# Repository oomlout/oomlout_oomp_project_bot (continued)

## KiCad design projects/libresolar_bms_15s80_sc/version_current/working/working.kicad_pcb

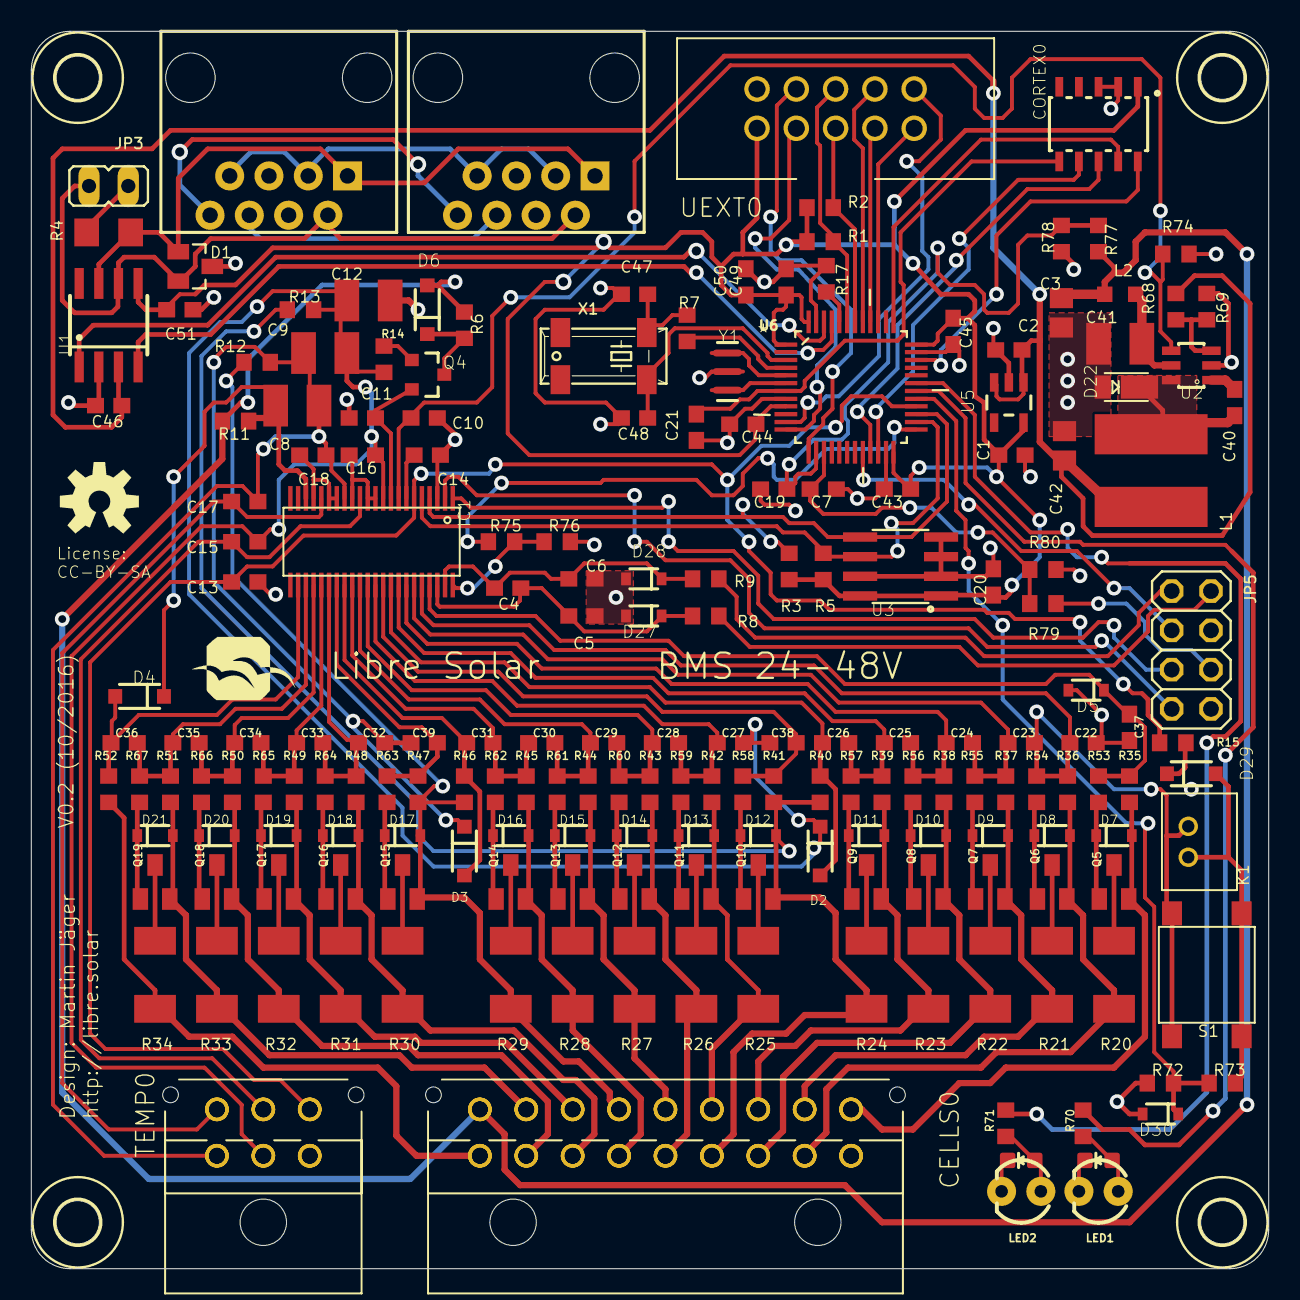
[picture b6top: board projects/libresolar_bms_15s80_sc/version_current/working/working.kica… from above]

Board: 2 copper layers, 80.0 x 80.0 mm, 201 parts (0 on the bottom side), 133 nets.

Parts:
C1, C50: 2.2µ; C0603
C2, C10, C11, C14, C16, C18: 1µ; C0603
C3: 1µ; C0805
C4, C5, C6, C7, C19, C20, C21, C22, C23, C24, C25, C26, C27, C28, C29, C30, C31, C32, C33, C34, C35, C36, C37, C38, C39, C40, C43, C44, C45, C46, C49, C51: 100n; C0603
C8, C9, C12: 10µ; C1210
C13, C15, C17: 4.7n; C0603
C41: 2.2µ; C1210
C42: 22µ; C0805
C47, C48: 4.3p; C0603
CELLS0: 66201821022
CORTEX0: CORTEX_DEBUGSMD; SAMTECH_FTSH-105-01
D1: NUP2105L; SOT23
D2, D3, D4, D6, D29: 1N4148W; SOD-123
D5, D27, D28, D30: 3.3V; SOD-323
D7, D8, D9, D10, D11, D12, D13, D14, D15, D16, D17, D18, D19, D20, D21: 5.6V; SOD-323
D22: DFLS1100-7; POWERDI123
D24, D26: LED-0603
H1, H2, H3, H4: MOUNT-HOLE2.8; 2,8
IC1: BQ76940; TSSOP44
JP1, JP2: RJ45; RJ45-8
JP3: JP1
JP5: 2X04
K1: 62000211622
K4: 66200621122
K5: 66201821122
L1: 47uH; WE-TPC_6823
L2: 4.7uH; L2012C
LED1, LED2: LED3MM
N1: OSHW-LOGOM; OSHW-LOGO-M
Q4: BSS123; SOT23-3
Q5, Q6, Q7, Q8, Q9, Q10, Q11, Q12, Q13, Q14, Q15, Q16, Q17, Q18, Q19: DMN2004K; SOT23
R1, R2, R3, R5: 2.2k; R0603
R4: 120; R1206
R6: t.b.d.; R0603
R7: 0R; R0603
R8, R9, R35, R36, R37, R38, R39, R40, R41, R42, R43, R44, R45, R46, R47, R48, R49, R50, R51, R52, R75: 1k; R0603
R11, R12, R13: 100; R0603
R14, R72, R74, R77, R79: 100k; R0603
R15, R78, R80: 5.6k; R0603
R17, R53, R54, R55, R56, R57, R58, R59, R60, R61, R62, R63, R64, R65, R66, R67, R69, R73: 10k; R0603
R20, R21, R22, R23, R24, R25, R26, R27, R28, R29, R30, R31, R32, R33, R34: 33; R2010
R68: 56k; R0603
R70, R71: 330; R0603
R76: 1M; R0603
S1: 430182050816
TEMP0: 66200621022
U1: TJA1042T/3; SOIC-8-N
U2: LMR16006X; SOT23-6
U3: M24256-BW; SO08
U5: MIC5225; SOT23-5
U6: STM32F072CB; QFP50P900X900X160-48N
U$1: LIBRESOLAR_LOGO
UEXT0: UEXT
X1: ABS25-32.768KHZ-6; MM20SS
Y1: 8MHz; RESONATOR-SMD-1_1

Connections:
+3V3: C1.1, C20.1, C43.1, C44.1, C45.1, C49.1, C50.1, C51.1, CORTEX0.1, R1.2, R2.2, R3.2, R5.2, U1.5, U3.1, U3.8, U5.5, U6.1, U6.9, U6.24, U6.36, U6.48, UEXT0.1
+5V: C2.1, C42.1, C46.1, L1.2, R68.2, U1.3, U5.1, U5.3
ALERT: IC1.44, R75.1, R76.2
ALERT_IN: R75.2, U6.25
BAT: C8.1, D4.C, IC1.20, R11.2
BTN: D30.C, R72.2, R73.1, U6.29
C0: CELLS0.10, D7.A, K5.10, Q5.2, R35.1
C1: CELLS0.2, D8.A, K5.2, Q6.2, R20.1, R36.1
C2: CELLS0.11, D9.A, K5.11, Q7.2, R21.1, R37.1
C3: CELLS0.3, D10.A, K5.3, Q8.2, R22.1, R38.1
C4: CELLS0.12, D11.A, K5.12, Q9.2, R23.1, R39.1
C5: CELLS0.4, D12.A, K5.4, Q10.2, R13.1, R24.1, R40.1, R41.1
C6: CELLS0.13, D13.A, K5.13, Q11.2, R25.1, R42.1
C7: CELLS0.5, D14.A, K5.5, Q12.2, R26.1, R43.1
C8: CELLS0.14, D15.A, K5.14, Q13.2, R27.1, R44.1
C9: CELLS0.6, D16.A, K5.6, Q14.2, R28.1, R45.1
C10: CELLS0.15, D17.A, K5.15, Q15.2, R12.1, R29.1, R46.1, R47.1
C11: CELLS0.7, D18.A, K5.7, Q16.2, R30.1, R48.1
C12: CELLS0.16, D19.A, K5.16, Q17.2, R31.1, R49.1
C13: CELLS0.8, D20.A, K5.8, Q18.2, R32.1, R50.1
C14: CELLS0.17, D21.A, K5.17, Q19.2, R33.1, R51.1
C15: CELLS0.9, K5.9, R34.1, R52.1
CAN_GND: JP1.3, JP1.7, JP2.3, JP2.7
CAN_H: D1.1, JP1.1, JP2.1, R4.1, U1.7
CAN_L: D1.2, JP1.2, JP2.2, JP3.2, U1.6
CAN_RX: U1.4, U6.45
CAN_SHLD: JP1.6, JP2.6
CAN_TX: U1.1, U6.46
CAN_V+: JP1.8, JP2.8
CAP1: C14.1, IC1.7
CAP2: C16.1, IC1.11, IC1.12, IC1.14
CAP3: C18.1, IC1.16, IC1.17, IC1.19
CHG_EN: IC1.2, JP5.2
DSG_EN: IC1.1, JP5.4
GND: C1.2, C2.2, C3.2, C5.2, C6.2, C7.2, C10.2, C11.2, C12.2, C13.2, C14.2, C19.2, C20.2, C21.2, C22.2, C37.2, C41.2, C42.2, C43.2, C44.2, C45.2, C46.2, C47.2, C48.2, C49.2, C50.2, C51.2, CELLS0.1, CORTEX0.3, CORTEX0.5, D1.3, D5.A, D22.A, D24.C, D26.C, D27.A, D28.A, D30.A, IC1.3, K4.1, K5.1, LED1.K, LED2.K, R17.1, R69.1, R72.1, R74.1, R76.1, R78.1, R80.1, TEMP0.1, U1.2, U2.2, U3.2, U3.3, U3.4, U3.7, U5.2, U6.8, U6.23, U6.35, U6.47, UEXT0.2, Y1.2
I2C1_SCL: R2.1, U6.42, UEXT0.5
I2C1_SDA: R1.1, U6.43, UEXT0.6
I2C2_SCL: IC1.5, R5.1, U3.6, U6.26
I2C2_SDA: IC1.4, R3.1, U3.5, U6.27
LED1: R70.2, U6.30
LED2: R71.2, U6.31
LOAD+: JP5.3, R79.2
MCU_IN: D29.A, K1.1, R73.2, S1.2, S1.4
unnamed: Q15.3, R30.2
unnamed: Q16.3, R31.2
unnamed: Q17.3, R32.2
unnamed: D19.C, Q17.1, R65.2
unnamed: Q6.3, R21.2
unnamed: D18.C, Q16.1, R64.2
unnamed: D7.C, Q5.1, R53.2
unnamed: C41.1, L2.1, U2.5
unnamed: D29.C, R15.2
unnamed: R68.1, R69.2, U2.3
unnamed: D8.C, Q6.1, R54.2
unnamed: D9.C, Q7.1, R55.2
unnamed: Q5.3, R20.2
unnamed: Q7.3, R22.2
unnamed: D10.C, Q8.1, R56.2
unnamed: Q8.3, R23.2
unnamed: Q9.3, R24.2
unnamed: D11.C, Q9.1, R57.2
unnamed: D12.C, Q10.1, R58.2
unnamed: Q10.3, R25.2
unnamed: Q11.3, R26.2
unnamed: D13.C, Q11.1, R59.2
unnamed: D14.C, Q12.1, R60.2
unnamed: Q12.3, R27.2
unnamed: D15.C, Q13.1, R61.2
unnamed: Q13.3, R28.2
unnamed: Q14.3, R29.2
unnamed: D16.C, Q14.1, R62.2
unnamed: D17.C, Q15.1, R63.2
unnamed: D20.C, Q18.1, R66.2
unnamed: Q18.3, R33.2
unnamed: D21.C, Q19.1, R67.2
unnamed: Q19.3, R34.2
unnamed: C40.2, D22.C, L1.1, U2.6
unnamed: C40.1, U2.1
unnamed: JP3.1, R4.2
unnamed: R7.1, U6.4
unnamed: C47.1, R7.2, X1.1
unnamed: D24.A, LED1.A, R70.1
unnamed: C48.1, U6.3, X1.4
unnamed: D26.A, LED2.A, R71.1
unnamed: D6.C, Q4.3, R6.2
unnamed: Q4.1, R14.2
unnamed: R17.2, U6.44
OSC_IN: U6.5, Y1.1
OSC_OUT: U6.6, Y1.3
PCHG_EN: JP5.6, U6.20
PWR: C3.1, CELLS0.18, D6.A, K5.18, L2.2, R6.1, R11.1, R77.2
REGOUT: C10.1, IC1.8, R74.2, U2.4
REGSRC: C11.1, IC1.9, Q4.2
R_SENSE+: JP5.7, R8.1
R_SENSE-: JP5.8, R9.1
SPI1_MISO: U6.40, UEXT0.7
SPI1_MOSI: U6.41, UEXT0.8
SPI1_SCK: U6.39, UEXT0.9
SRN: C4.2, C6.1, D28.C, IC1.43, R9.2
SRP: C4.1, C5.1, D27.C, IC1.42, R8.2
SSEL: U6.11, UEXT0.10
SWCLK: CORTEX0.4, U6.37
SWDIO: CORTEX0.2, U6.34
TS1: C13.1, IC1.6, K4.4, R15.1, TEMP0.4, U6.28
TS2: C15.1, IC1.13, K4.5, TEMP0.5
TS3: C17.1, IC1.18, K4.6, TEMP0.6
USART2_RX: U6.13, UEXT0.4
USART2_TX: U6.12, UEXT0.3
USART3_RX: CORTEX0.8, U6.22
USART3_TX: CORTEX0.6, U6.21
VC0: C37.1, D5.C, IC1.41, R35.2, R53.1
VC1: C22.1, C23.2, IC1.40, K1.2, R36.2, R54.1, S1.1, S1.3
VC2: C23.1, C24.2, IC1.39, R37.2, R55.1
VC3: C24.1, C25.2, IC1.38, R38.2, R56.1
VC4: C25.1, C26.2, IC1.37, R39.2, R57.1
VC5: C26.1, D2.A, IC1.36, R40.2
VC5B: C38.2, IC1.35, R41.2, R58.1
VC5X: C9.2, C12.1, C15.2, C16.2, C27.2, C38.1, D2.C, IC1.10, K4.2, R13.2, R14.1, TEMP0.2
VC6: C27.1, C28.2, IC1.34, R42.2, R59.1
VC7: C28.1, C29.2, IC1.33, R43.2, R60.1
VC8: C29.1, C30.2, IC1.32, R44.2, R61.1
VC9: C30.1, C31.2, IC1.31, R45.2, R62.1
VC10: C31.1, D3.A, IC1.30, R46.2
VC10B: C39.2, IC1.29, R47.2, R63.1
VC10X: C8.2, C9.1, C17.2, C18.2, C32.2, C39.1, D3.C, IC1.15, K4.3, R12.2, TEMP0.3
VC11: C32.1, C33.2, IC1.28, R48.2, R64.1
VC12: C33.1, C34.2, IC1.27, R49.2, R65.1
VC13: C34.1, C35.2, IC1.26, R50.2, R66.1
VC14: C35.1, C36.2, IC1.25, R51.2, R67.1
VC15: C36.1, D4.A, IC1.24, R52.2
V_BAT: C19.1, R77.1, R78.2, U6.14
V_LOAD: C7.1, R79.1, R80.2, U6.15
~RESET: C21.1, CORTEX0.10, U6.7

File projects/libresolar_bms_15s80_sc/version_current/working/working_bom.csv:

"Id";"Designator";"Footprint";"Quantity";"Designation";"Supplier and ref";
1;"Q9,Q7,Q8,Q14,Q10,Q13,Q5,Q16,Q6,Q11,Q17,Q18,Q12,Q19,Q15";"SOT23";15;"DMN2004K";;;
2;"C31,C29,C25,C19,C7,C20,C28,C36,C30,C21,C51,C32,C45,C40,C5,C37,C26,C49,C46,C22,C35,C27,C24,C23,C34,C43,C38,C6,C44,C39,C4,C33";"C0603";32;"100n";;;
3;"R59,R66,R64,R58,R62,R56,R53,R63,R60,R69,R57,R67,R61,R73,R65,R17,R54,R55";"R0603";18;"10k";;;
4;"R79,R74,R77,R14,R72";"R0603";5;"100k";;;
5;"R42,R50,R44,R43,R75,R37,R48,R40,R49,R8,R9,R35,R38,R47,R46,R52,R39,R45,R41,R36,R51";"R0603";21;"1k";;;
6;"R12,R11,R13";"R0603";3;"100";;;
7;"C48,C47";"C0603";2;"4.3p";;;
8;"R26,R22,R23,R21,R32,R28,R33,R27,R20,R31,R25,R34,R30,R29,R24";"R2010";15;"33";;;
9;"CORTEX0";"SAMTECH_FTSH-105-01";1;"CORTEX_DEBUGSMD";;;
10;"D6,D3,D29,D4,D2";"SOD-123";5;"1N4148W";;;
11;"U$1";"LIBRESOLAR_LOGO";1;"LIBRESOLAR_LOGO";;;
12;"Q4";"SOT23-3";1;"BSS123";;;
13;"C41";"C1210";1;"2.2µ";;;
14;"D14,D21,D11,D12,D15,D17,D16,D19,D9,D18,D8,D20,D7,D13,D10";"SOD-323";15;"5.6V";;;
15;"R76";"R0603";1;"1M";;;
16;"D30,D28,D5,D27";"SOD-323";4;"3.3V";;;
17;"C1,C50";"C0603";2;"2.2µ";;;
18;"R4";"R1206";1;"120";;;
19;"C14,C2,C18,C10,C11,C16";"C0603";6;"1µ";;;
20;"C13,C17,C15";"C0603";3;"4.7n";;;
21;"K5";"66201821122";1;"66201821122";;;
22;"H3,H2,H4,H1";"2,8";4;"MOUNT-HOLE2.8";;;
23;"U1";"SOIC-8-N";1;"TJA1042T/3";;;
24;"IC1";"TSSOP44";1;"BQ76940";;;
25;"Y1";"RESONATOR-SMD-1_1";1;"8MHz";;;
26;"U6";"QFP50P900X900X160-48N";1;"STM32F072CB";;;
27;"LED1,LED2";"LED3MM";2;"";;;
28;"R68";"R0603";1;"56k";;;
29;"N1";"OSHW-LOGO-M";1;"OSHW-LOGOM";;;
30;"D1";"SOT23";1;"NUP2105L";;;
31;"K1";"62000211622";1;"62000211622";;;
32;"C42";"C0805";1;"22µ";;;
33;"U5";"SOT23-5";1;"MIC5225";;;
34;"C9,C12,C8";"C1210";3;"10µ";;;
35;"R78,R80,R15";"R0603";3;"5.6k";;;
36;"D24,D26";"LED-0603";2;"";;;
37;"R70,R71";"R0603";2;"330";;;
38;"R5,R2,R3,R1";"R0603";4;"2.2k";;;
39;"R7";"R0603";1;"0R";;;
40;"S1";"430182050816";1;"";;;
41;"R6";"R0603";1;"t.b.d.";;;
42;"JP3";"JP1";1;"";;;
43;"D22";"POWERDI123";1;"DFLS1100-7";;;
44;"U2";"SOT23-6";1;"LMR16006X";;;
45;"L1";"WE-TPC_6823";1;"47uH";;;
46;"C3";"C0805";1;"1µ";;;
47;"UEXT0";"UEXT";1;"UEXT";;;
48;"X1";"MM20SS";1;"ABS25-32.768KHZ-6";;;
49;"JP2,JP1";"RJ45-8";2;"RJ45";;;
50;"L2";"L2012C";1;"4.7uH";;;
51;"U3";"SO08";1;"M24256-BW";;;
52;"CELLS0";"66201821022";1;"";;;
53;"JP5";"2X04";1;"";;;
54;"K4";"66200621122";1;"66200621122";;;
55;"TEMP0";"66200621022";1;"66200621022";;;

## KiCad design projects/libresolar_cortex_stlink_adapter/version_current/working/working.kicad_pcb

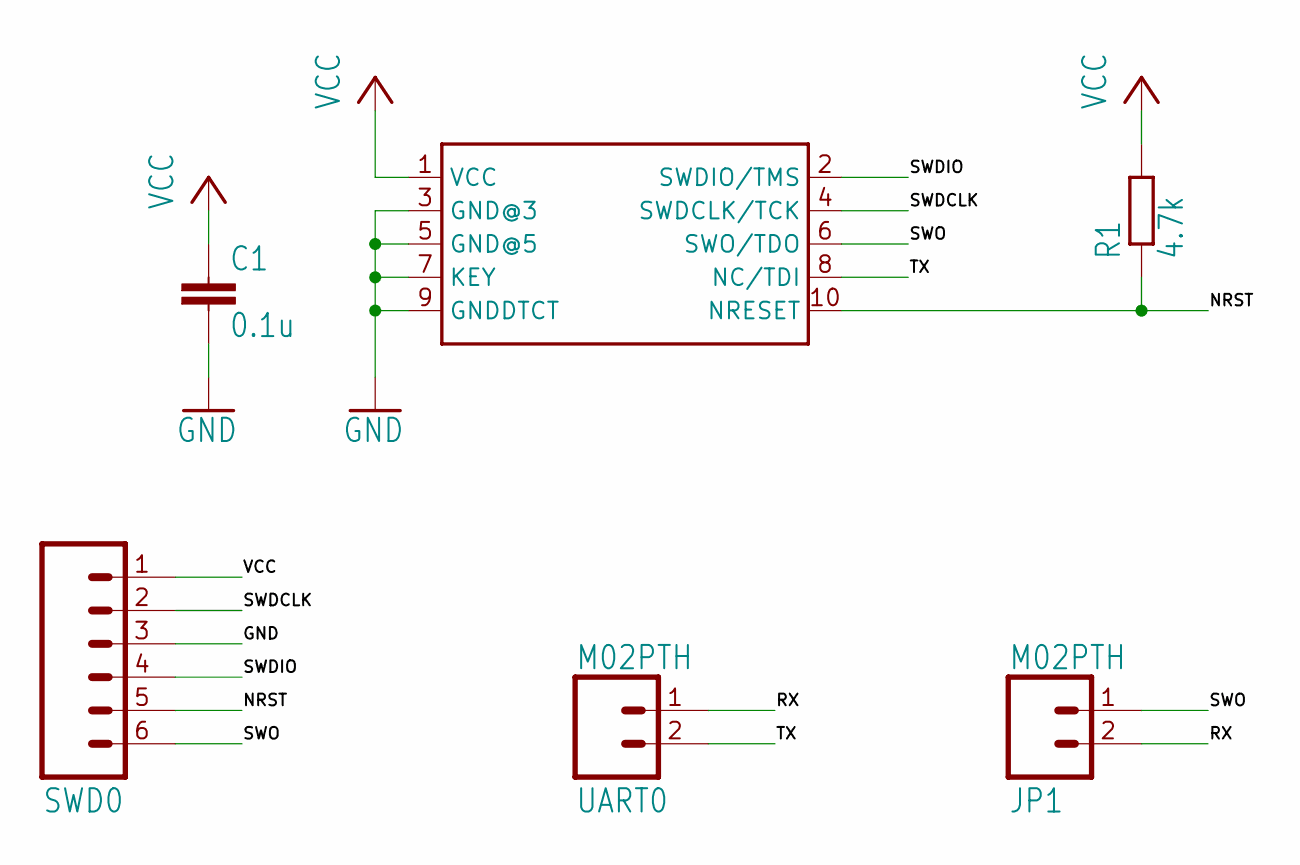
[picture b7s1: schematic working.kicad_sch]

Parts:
C1: 0.1u; C0805
CORTEX0: CORTEX_DEBUGPTH; 2X5-PTH-1.27MM
JP1: M02PTH; 1X02
R1: 4.7k; R0805
SWD0: M06SILK_FEMALE_PTH; 1X06
UART0: M02PTH; 1X02

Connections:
GND: C1.2, CORTEX0.3 (GND@3), CORTEX0.5 (GND@5), CORTEX0.7 (KEY), CORTEX0.9 (GNDDTCT), SWD0.3
NRST: CORTEX0.10 (NRESET), R1.1, SWD0.5
RX: JP1.2, UART0.1
SWDCLK: CORTEX0.4 (SWDCLK/TCK), SWD0.2
SWDIO: CORTEX0.2 (SWDIO/TMS), SWD0.4
SWO: CORTEX0.6 (SWO/TDO), JP1.1, SWD0.6
TX: CORTEX0.8 (NC/TDI), UART0.2
VCC: C1.1, CORTEX0.1 (VCC), R1.2, SWD0.1

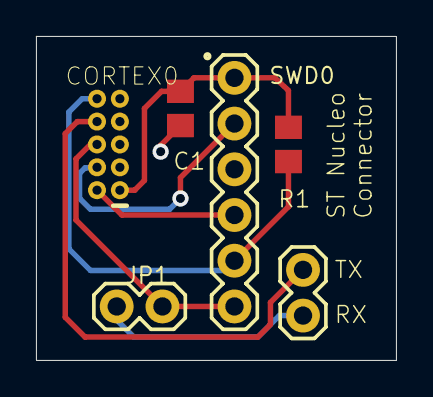
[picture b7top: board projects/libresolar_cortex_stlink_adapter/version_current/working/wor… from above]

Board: 2 copper layers, 20.0 x 18.0 mm, 6 parts (0 on the bottom side), 8 nets.

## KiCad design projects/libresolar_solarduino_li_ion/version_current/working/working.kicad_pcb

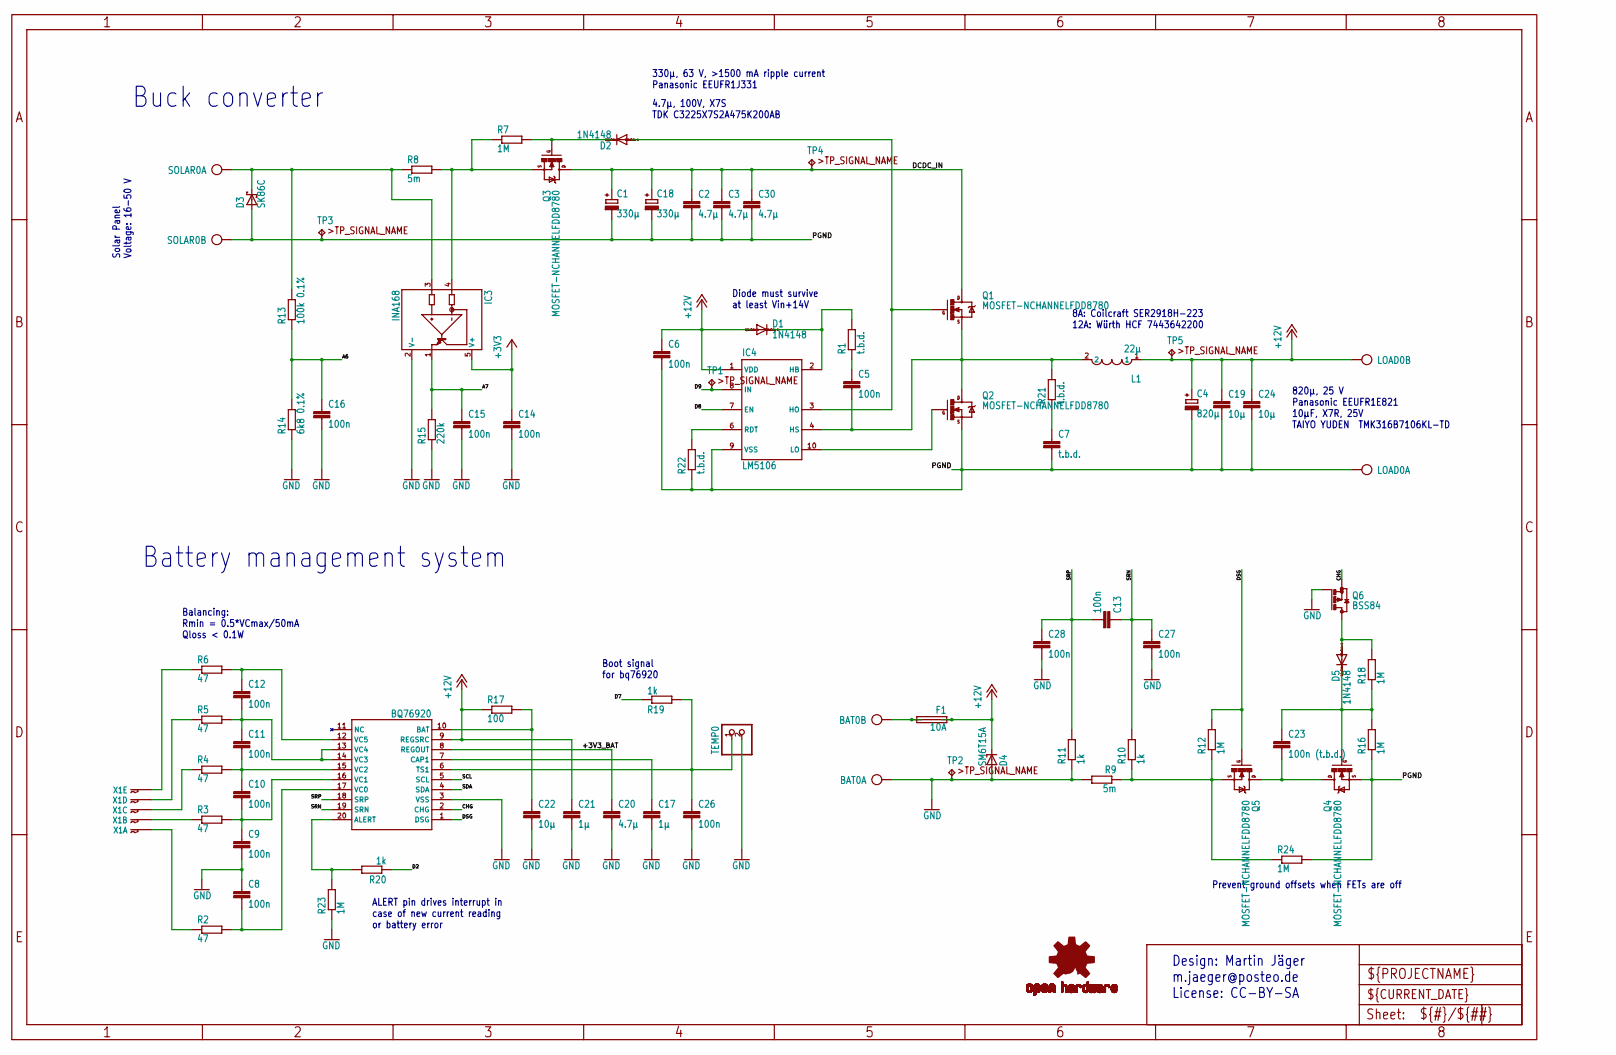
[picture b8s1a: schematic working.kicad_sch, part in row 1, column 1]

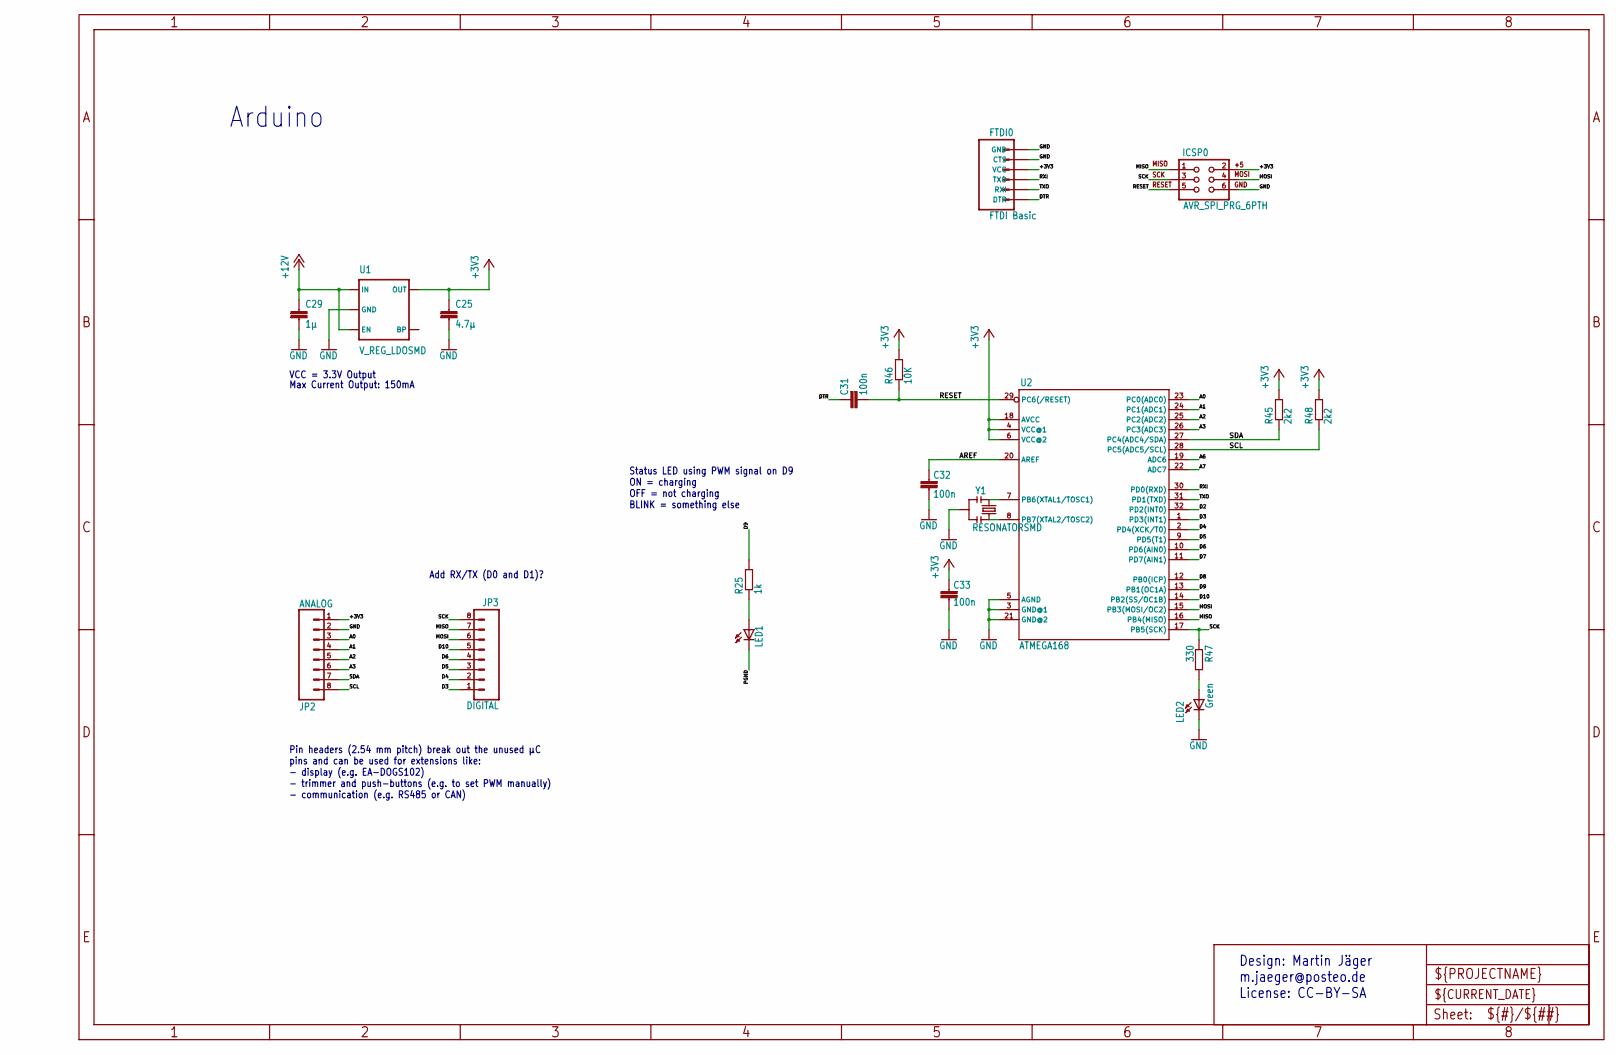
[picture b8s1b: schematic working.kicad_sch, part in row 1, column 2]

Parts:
BAT0: MKDS_5/2-9,52; MKDS_5_2-952
C1, C18: 330µ; E5-13; MPN EEUFR1J331B
C2, C3, C30: 4.7µ; C1210; MPN C3225X7S2A475K200AB
C4: 820µ; E5-10,5; MPN EEUFR1E821B
C5, C6, C8, C9, C10, C11, C12, C13, C14, C15, C16, C26, C27, C28, C31, C32: 100n; C0805; MPN 08055C104KAT2A
C7: t.b.d.; C0805; MPN 08055C104KAT2A
C17, C21, C29: 1µ; C0805; MPN 08053C105KAT2A
C19, C22, C24: 10µ; C1206; MPN TMK316B7106KL-TD
C20, C25: 4.7µ; C0805; MPN 0805YC475KAT2A
C23: 100n (t.b.d.); C0805; MPN 08055C104KAT2A
C33: 100n; C0805; MPN 08055C104JAT2A
D1, D2, D5: 1N4148; SOD323-R; MPN 1N4148WS-E3-08
D3: SK86C; SMC; MPN SK56C
D4: SM6T15A; SMB; MPN P6SMBJ15A
F1: 10A; SHK20Q
FTDI0: FTDI Basic; 1X06; MPN 2212S-06SG-85
IC2: BQ76920; TSSOP20
IC3: INA168; SOT23-5; MPN INA168NA/250.
IC4: LM5106; VSSOP10; MPN LM5106MM/NOPB
ICSP0: AVR_SPI_PRG_6PTH; 2X3
JP2: ANALOG; 1X08_ROUND
JP3: DIGITAL; 1X08_ROUND
L1: 22µ; WE-HCF_2818_7443643300; MPN SER2918H-223KL
LED1: LED3MM; MPN MCL034GD
LED2: Green; 0603-LED-ALT1; MPN MCL034GD
LOAD0: MKDS_5/2-9,52; MKDS_5_2-952
N1: OSHW-LOGOM; OSHW-LOGO-M
Q1, Q2, Q3: MOSFET-NCHANNELFDD8780; DPAK; MPN IRFR3607PBF
Q4, Q5: MOSFET-NCHANNELFDD8780; DPAK; MPN IRFR7440TRPBF
Q6: BSS84; SOT23; MPN BSS84-7-F
R1, R22: t.b.d.; R0805; MPN CR0805-FX-1001ELF
R2, R3, R4, R5, R6: 47; R2512; MPN MCHP122WF470JT4E
R7, R12, R16, R18, R23, R24: 1M; R0805; MPN CR0805-FX-1004ELF.
R8, R9: 5m; R2512; MPN CRF2512-FX-R005ELF
R10, R11, R19, R20, R25: 1k; R0805; MPN CR0805-FX-1001ELF
R13: 100k 0.1%; R0805; MPN ERA6AEB104V
R14: 6k8 0.1%; R0805; MPN ERA6AEB682V
R15: 220k; R0805; MPN CHV0805-FX-2203ELF
R17: 100; R0805; MPN CR0805-FX-1000-ELF
R21: t.b.d.; R2010; MPN CRM2010-JW-2R2ELF
R45, R48: 2k2; R0805; MPN CR0805-FX-1001ELF
R46: 10K; R0805; MPN CR0805-FX-1002ELF
R47: 330; R0805; MPN CR0805-FX-3300ELF
SOLAR0: MKDS_5/2-9,52; MKDS_5_2-952
TEMP0: PINHD-1X2/90; 1X02_90; MPN MC34745
TP1, TP2, TP3, TP4, TP5: TPPAD1-13; P1-13
U1: V_REG_LDOSMD; SOT23-5; MPN MIC5205-3.3YM5 TR
U2: ATMEGA168; TQFP32-08; MPN ATMEGA328P-AU
X1: 05-JST-S5B-XH-A; S5B-XH; MPN S5B-XH-A (LF)(SN)
Y1: RESONATORSMD; RESONATOR-SMD; MPN CSTCE8M00G55-R0

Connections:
+3V3: C14.1, C25.1, C33.2, FTDI0.4 (VCC), IC3.5 (V+), ICSP0.2, JP2.1, R45.2, R46.2, R48.2, U1.5 (OUT), U2.4 (VCC@1), U2.6 (VCC@2), U2.18 (AVCC)
+3V3_BAT: C20.1, IC2.8 (REGOUT)
+12V: C4.+, C6.1, C19.1, C21.1, C24.1, C29.1, D1.A, D4.C, F1.1A, F1.1B, IC2.9 (REGSRC), IC4.1 (VDD), L1.1, LOAD0.2, R17.1, TP5.TP, U1.1 (IN), U1.3 (EN)
A0: JP2.3, U2.23 (PC0(ADC0))
A1: JP2.4, U2.24 (PC1(ADC1))
A2: JP2.5, U2.25 (PC2(ADC2))
A3: JP2.6, U2.26 (PC3(ADC3))
A6: C16.1, R13.1, R14.2, U2.19 (ADC6)
A7: C15.1, IC3.1 (OUT), R15.2, U2.22 (ADC7)
ALERT: IC2.20 (ALERT), R20.2, R23.2
AREF: C32.2, U2.20 (AREF)
BAT+: BAT0.2, F1.2A, F1.2B
CHG: IC2.2 (CHG), Q6.2 (S)
D2: R20.1, U2.32 (PD2(INT0))
D3: JP3.1, U2.1 (PD3(INT1))
D4: JP3.2, U2.2 (PD4(XCK/T0))
D5: JP3.3, U2.9 (PD5(T1))
D6: JP3.4, U2.10 (PD6(AIN0))
D7: R19.1, U2.11 (PD7(AIN1))
D8: IC4.7 (EN), U2.12 (PB0(ICP))
D9: IC4.8 (IN), R25.2, TP1.TP, U2.13 (PB1(OC1A))
D10: JP3.5, U2.14 (PB2(SS/OC1B))
DCDC_IN: C1.+, C2.1, C3.1, C18.+, C30.1, Q1.4 (D), Q3.4 (D), TP4.TP
DSG: IC2.1 (DSG), Q5.1 (G), R12.2
DTR: C31.2, FTDI0.1 (DTR)
D_LS: C5.2, IC4.4 (HS), L1.2, Q1.3 (S), Q2.4 (D), R21.2
GND: BAT0.1, C8.1, C9.2, C14.2, C15.2, C16.2, C17.2, C20.2, C21.2, C22.2, C25.2, C26.2, C27.2, C28.2, C29.2, C32.1, C33.1, D4.A, FTDI0.5 (CTS), FTDI0.6 (GND), IC2.3 (VSS), IC3.2 (V-), ICSP0.6, JP2.2, LED2.C, Q6.1 (G), R9.2, R11.1, R14.1, R15.1, R23.1, TEMP0.2, TP2.TP, U1.2 (GND), U2.3 (GND@1), U2.5 (AGND), U2.21 (GND@2), Y1.2
MISO: ICSP0.1, JP3.7, U2.16 (PB4(MISO))
MOSI: ICSP0.4, JP3.6, U2.15 (PB3(MOSI/OC2))
unnamed: IC3.4 (IN-), Q3.3 (S), R7.1, R8.2
unnamed: IC4.10 (LO), Q2.1 (G)
unnamed: LED2.A, R47.2
unnamed: D2.A, IC4.3 (HO), Q1.1 (G)
unnamed: D1.C, IC4.2 (HB), R1.2
unnamed: C23.1, D5.C, Q4.1 (G), R16.2, R18.1
unnamed: R3.1, X1.P$2
unnamed: C5.1, R1.1
unnamed: C22.1, IC2.10 (BAT), R17.2
unnamed: C10.1, C11.2, IC2.15 (VC2), R4.2
unnamed: C11.1, C12.2, IC2.13 (VC4), IC2.14 (VC3), R5.2
unnamed: R2.1, X1.P$1
unnamed: C12.1, IC2.12 (VC5), R6.2
unnamed: C8.2, IC2.17 (VC0), R2.2
unnamed: R4.1, X1.P$3
unnamed: C9.1, C10.2, IC2.16 (VC1), R3.2
unnamed: R5.1, X1.P$4
unnamed: D5.A, Q6.3 (D), R18.2
unnamed: D2.C, Q3.1 (G), R7.2
unnamed: U2.8 (PB7(XTAL2/TOSC2)), Y1.3
unnamed: U2.7 (PB6(XTAL1/TOSC1)), Y1.1
unnamed: Q5.3 (S), R9.1, R10.1, R12.1, R24.1
unnamed: C23.2, Q4.4 (D), Q5.4 (D)
unnamed: IC4.6 (RDT), R22.2
unnamed: R6.1, X1.P$5
unnamed: C17.1, IC2.7 (CAP1)
unnamed: C7.1, R21.1
unnamed: LED1.A, R25.1
NTC: C26.1, IC2.6 (TS1), R19.2, TEMP0.1
PGND: C1.-, C2.2, C3.2, C4.-, C6.2, C7.2, C18.-, C19.2, C24.2, C30.2, D3.A, IC4.9 (VSS), LED1.K (C), LOAD0.1, Q2.3 (S), Q4.3 (S), R16.1, R22.1, R24.2, SOLAR0.2, TP3.TP
RESET: C31.1, ICSP0.5, R46.1, U2.29 (PC6(/RESET))
RXI: FTDI0.3 (TXO), U2.30 (PD0(RXD))
SCK: ICSP0.3, JP3.8, R47.1, U2.17 (PB5(SCK))
SCL: IC2.5 (SCL), JP2.8, R48.1, U2.28 (PC5(ADC5/SCL))
SDA: IC2.4 (SDA), JP2.7, R45.1, U2.27 (PC4(ADC4/SDA))
SOLAR+: D3.C, IC3.3 (IN+), R8.1, R13.2, SOLAR0.1
SRN: C13.1, C27.1, IC2.19 (SRN), R10.2
SRP: C13.2, C28.1, IC2.18 (SRP), R11.2
TXO: FTDI0.2 (RXI), U2.31 (PD1(TXD))

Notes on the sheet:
Pin headers (2.54 mm pitch) break out the unused µC pins and can be used for extensions like: - display (e.g. EA-DOGS102) - trimmer and push-buttons (e.g. to set PWM manually) - communication (e.g. RS485 or CAN)
820µ, 25 V Panasonic EEUFR1E821 10µF, X7R, 25V TAIYO YUDEN TMK316B7106KL-TD
Boot signal for bq76920
Max Current Output: 150mA
ALERT pin drives interrupt in case of new current reading or battery error
VCC = 3.3V Output
Solar Panel Voltage: 16-50 V
4.7µ, 100V, X7S TDK C3225X7S2A475K200AB
Arduino
330µ, 63 V, >1500 mA ripple current Panasonic EEUFR1J331
Diode must survive at least Vin+14V
8A: Coilcraft SER2918H-223 12A: Würth HCF 7443642200
Buck converter
Battery management system
Prevent ground offsets when FETs are off
Status LED using PWM signal on D9 ON = charging OFF = not charging BLINK = something else
Design: Martin Jäger m.jaeger@posteo.de License: CC-BY-SA
Add RX/TX (D0 and D1)?
Balancing: Rmin = 0.5*VCmax/50mA Qloss < 0.1W

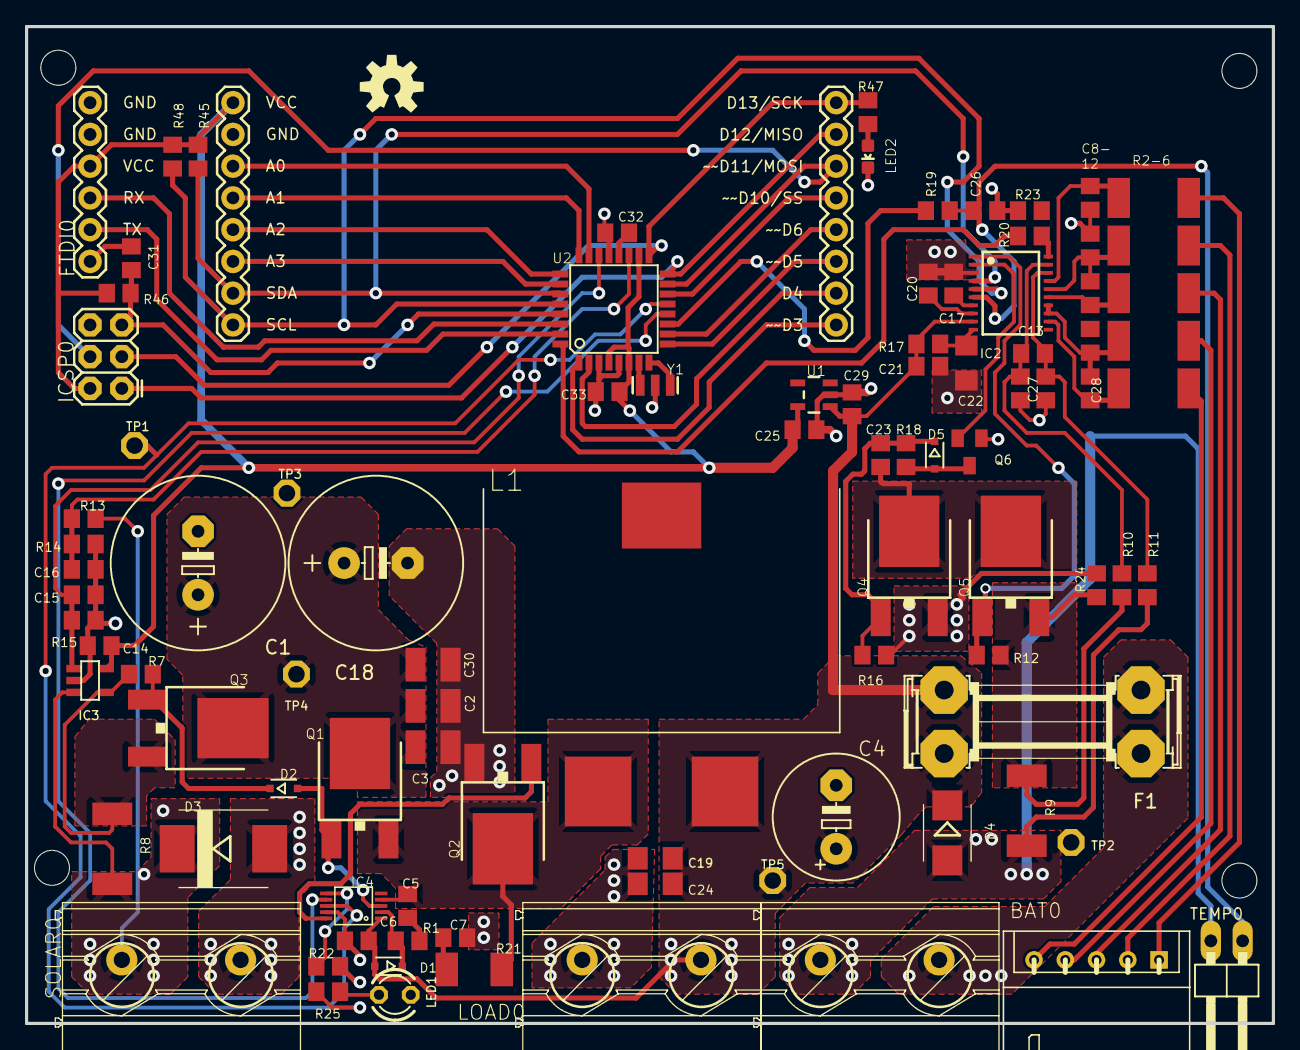
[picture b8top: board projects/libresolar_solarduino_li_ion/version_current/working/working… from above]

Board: 2 copper layers, 99.7 x 79.7 mm, 102 parts (0 on the bottom side), 68 nets.

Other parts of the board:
@HOLE0, @HOLE1, @HOLE2, @HOLE3: (no value)

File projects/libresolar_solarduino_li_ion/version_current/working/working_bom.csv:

"Id";"Designator";"Footprint";"Quantity";"Designation";"Supplier and ref";
1;"R45,R48";"R0805";2;"2k2";;;
2;"C17,C21,C29";"C0805";3;"1µ";;;
3;"C3,C30,C2";"C1210";3;"4.7µ";;;
4;"C19,C24,C22";"C1206";3;"10µ";;;
5;"C28,C27,C13,C15,C32,C33,C26,C14,C16,C9,C12,C5,C6,C10,C11,C8,C31";"C0805";17;"100n";;;
6;"Q3,Q1,Q2";"DPAK";3;"IRFR3607";;;
7;"R47";"R0805";1;"330";;;
8;"C18,C1";"E5-13";2;"330µ";;;
9;"@HOLE3,@HOLE1,@HOLE2,@HOLE0";"";4;"";;;
10;"R13";"R0805";1;"100k 0.1%";;;
11;"JP3";"1X08_ROUND";1;"DIGITAL";;;
12;"ICSP0";"2X3";1;"AVR_SPI_PRG_6PTH";;;
13;"X1";"S5B-XH";1;"JST-XH-2.5";;;
14;"Q4";"DPAK";1;"IRFB7440";;;
15;"FTDI0";"1X06";1;"FTDI Basic";;;
16;"R9,R8";"R2512";2;"5m";;;
17;"R3,R2,R5,R6,R4";"R2512";5;"47";;;
18;"D2,D1,D5";"SOD323-R";3;"1N4148";;;
19;"C7";"C0805";1;"t.b.d.";;;
20;"TEMP0";"1X02_90";1;"";;;
21;"R12,R23,R16,R24,R18,R7";"R0805";6;"1M";;;
22;"R20,R19,R10,R25,R11";"R0805";5;"1k";;;
23;"TP4,TP2,TP3,TP5,TP1";"P1-13";5;"TPPAD1-13";;;
24;"U1";"SOT23-5";1;"MIC5205";;;
25;"Y1";"RESONATOR-SMD";1;"8MHz";;;
26;"C23";"C0805";1;"100n (t.b.d.)";;;
27;"LED1";"LED3MM";1;"";;;
28;"IC2";"TSSOP20";1;"BQ76920";;;
29;"D3";"SMC";1;"SK86C";;;
30;"IC3";"SOT23-5";1;"INA168";;;
31;"R1,R22";"R0805";2;"t.b.d.";;;
32;"C4";"E5-10,5";1;"820µ";;;
33;"R21";"R2010";1;"t.b.d.";;;
34;"R14";"R0805";1;"6k8 0.1%";;;
35;"LED2";"0603-LED-ALT1";1;"Green";;;
36;"BAT0,LOAD0,SOLAR0";"MKDS_5_2-952";3;"MKDS_5/2-9,52";;;
37;"JP2";"1X08_ROUND";1;"ANALOG";;;
38;"D4";"SMB";1;"SM6T15A";;;
39;"L1";"WE-HCF_2818_7443643300";1;"22µ";;;
40;"R15";"R0805";1;"220k";;;
41;"C25,C20";"C0805";2;"4.7µ";;;
42;"R17";"R0805";1;"100";;;
43;"Q5";"DPAK";1;"IRFR7440";;;
44;"F1";"SHK20Q";1;"10A";;;
45;"R46";"R0805";1;"10K";;;
46;"N1";"OSHW-LOGO-M";1;"OSHW-LOGOM";;;
47;"Q6";"SOT23";1;"BSS84";;;
48;"IC4";"VSSOP10";1;"LM5106";;;
49;"U2";"TQFP32-08";1;"ATMEGA328P";;;
